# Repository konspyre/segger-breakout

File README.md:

# Segger SWD/JTAG Breakout Board

<a href="https://oshpark.com/shared_projects/w7QyiW3S"></img></a>

A breakout board for the Segger J-Link (2.54mm pitch) to SWD (1.27mm pitch) headers. Includes silkscreen pinouts for both 2.54mm and 1.27mm pitch connections with mirroring on the opposite sides, and a broken out header area for point-to-point connections.

### Parts

| Quantity | Description                           | Digikey Part Number |
| -        | -                                     | -                   |
| 1        | 2.54mm header (Segger to board)       | [D2520-6002-AR](https://www.digikey.com/products/en?keywords=D2520-6002-AR) | 
| 1        | 1.27mm header  (Board to SWD)         | [952-1383-ND](https://www.digikey.com/products/en?keywords=952-1383-ND)     |

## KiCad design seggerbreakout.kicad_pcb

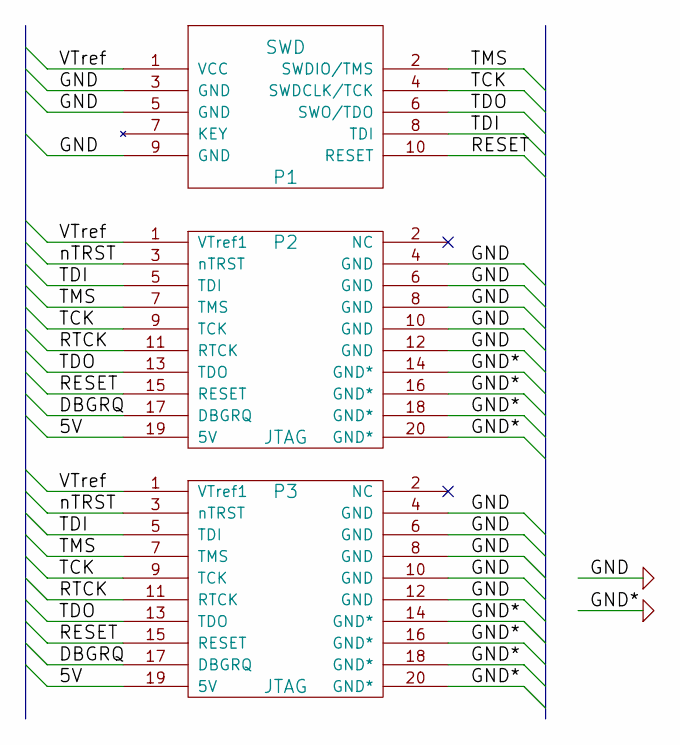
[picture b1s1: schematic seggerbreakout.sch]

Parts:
P1: SWD
P2, P3: JTAG

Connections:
/5V: P2.19 (5V), P3.19 (5V)
/DBGRQ: P2.17 (DBGRQ), P3.17 (DBGRQ)
/RESET: P1.10 (RESET), P2.15 (RESET), P3.15 (RESET)
/RTCK: P2.11 (RTCK), P3.11 (RTCK)
/TCK: P1.4 (SWDCLK/TCK), P2.9 (TCK), P3.9 (TCK)
/TDI: P1.8 (TDI), P2.5 (TDI), P3.5 (TDI)
/TDO: P1.6 (SWO/TDO), P2.13 (TDO), P3.13 (TDO)
/TMS: P1.2 (SWDIO/TMS), P2.7 (TMS), P3.7 (TMS)
/VTref: P1.1 (VCC), P2.1 (VTref1), P3.1 (VTref1)
/nTRST: P2.3 (nTRST), P3.3 (nTRST)
GND: P1.3 (GND), P1.5 (GND), P1.9 (GND), P2.4 (GND), P2.6 (GND), P2.8 (GND), P2.10 (GND), P2.12 (GND), P2.14 (GND*), P2.16 (GND*), P2.18 (GND*), P2.20 (GND*), P3.4 (GND), P3.6 (GND), P3.8 (GND), P3.10 (GND), P3.12 (GND), P3.14 (GND*), P3.16 (GND*), P3.18 (GND*), P3.20 (GND*)

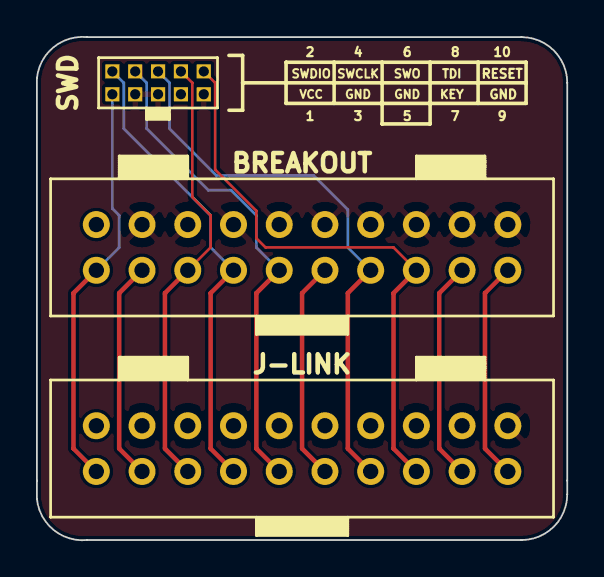
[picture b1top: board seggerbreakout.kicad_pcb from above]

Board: 2 copper layers, 29.5 x 28.0 mm, 3 parts (0 on the bottom side), 11 nets.

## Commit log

2014-03-20 Add seggerbreakout, a breakout to the 20P IDC connector the Segger EDU provides
2014-03-22 Add footprints
2014-04-01 Add swd
2014-04-18 Add a breakout portion for jtag connector
2014-06-05 Add segger 20pin connector
2014-08-18 add swd and 2x5 swd connector
2014-08-18 Add cleaner bus routed version
2014-08-18 Sent out for fabrication
    Vendor: OSHPark, LLC
2014-08-29 fix hole sizes!
2014-08-30 Hole resize and rerouting
2014-08-31 Sent to fab
    Vendor: OSHPark, LLC
2014-09-11 Multiple fixes from last fabbed revision
    1. Enlarged annular rings on SWD breakout and made them square, for better solderability
    2. On the last revision, I flipped the large pin headers for ease of use with the SWD connector cable,
    however I neglected to also flip the silkscreen indicators as well. This has been fixed.
    3. Corrected the silkscreen for the large pin headers, they were a bit larger than the actual keyed tabs.
    Parts:
    20P header: D2520-6002-AR - Vendor: Mouser
2014-09-11 Update fill zones
2014-09-12 Update tracks and routing to be cleaner and submit to fabrication
    Board vendor: OSHPark, LLC
    Board date: 2014-09-12
2014-09-12 Add final version sent to fab
2014-09-30 Improve thermals for PTH->ground plane connections
2014-10-01 Add a SWD guide (incorrect for now due to upside down reading of segger docs)
2014-10-02 Correct SWD pinout on schematic and footprint
2014-10-02 Update SWD pinout guide and correct schematics to be proper
2014-10-03 Add front-side silkscreen for segger breakout
2014-10-03 Re-route TDO trace (it wrapped around before)
2014-10-03 Production gerbers, board date 10-1-2014
    Fabricator: OSHPark, LLC
2019-03-11 Add board pictures and documentation
2019-03-11 Add fabrication link
2019-03-11 Add .gitignore for KiCAD
2019-03-11 Create LICENSE
2020-12-24 README: Update badge, add table for parts
2021-01-29 J-Link: Add image of board
